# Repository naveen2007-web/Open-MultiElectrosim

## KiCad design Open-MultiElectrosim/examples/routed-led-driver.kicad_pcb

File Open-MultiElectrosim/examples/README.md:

# Importable starter projects

Use Export → Import an existing project in the app and select any `.ome.json` file here. The same starters are also available from Examples.

- `rc.ome.json`: RC low-pass, sine source, two differential probes.
- `divider.ome.json`: 10 V / two equal 1 kΩ resistors / 5 V midpoint.
- `logic.ome.json`: AND followed by NOT, with toggle inputs.
- `blink.ome.json`: powered Arduino logical GPIO interpreter driving an LED through 330 Ω.
- `opamp.ome.json`: finite-gain voltage follower.
- `pcb.ome.json`: complete LED circuit with a compact routed board; zero issues under implemented DRC checks.
- `routed-led-driver.kicad_pcb`: directly exported generic LED board for KiCad review.

The KiCad file is a generic starting point, not a manufacturer-qualified layout. Read README.md and docs/MODELS.md before fabrication or drawing conclusions about real hardware.

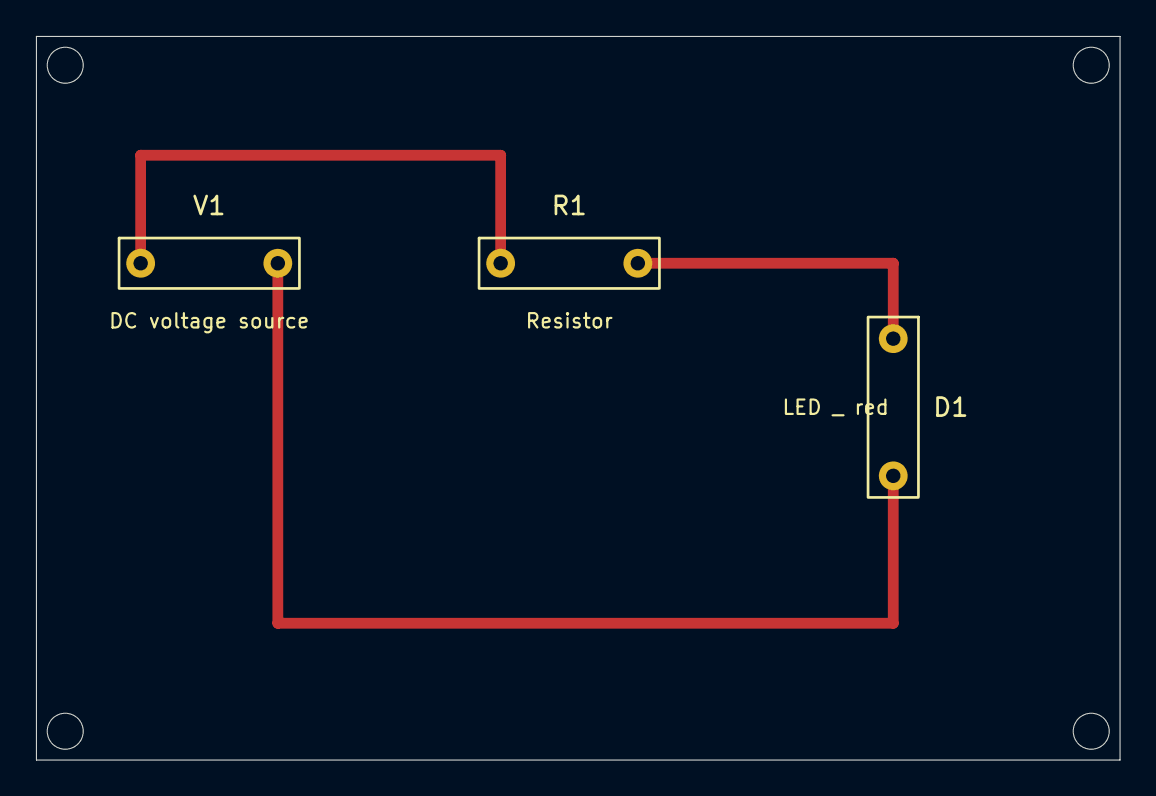
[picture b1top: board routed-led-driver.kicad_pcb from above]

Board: 2 copper layers, 60.2 x 40.2 mm, 3 parts (0 on the bottom side), 3 nets.

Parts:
D1: LED _ red; Generic_2Pin
R1: Resistor; Generic_2Pin
V1: DC voltage source; Generic_2Pin

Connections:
GND: D1.2, V1.2
Net-1: R1.1, V1.1
Net-2: D1.1, R1.2
